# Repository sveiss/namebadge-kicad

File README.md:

namebadge-kicad
===============

This repo contains the Kicad data files for an animated desk toy/namebadge with the letter K, built using WS2812 LEDs (Adafruit "NeoPixels") and a Raspberry Pi Pico.

*Note*: This is my first electronics project in a very long while -- don't use this project as an example of how to do things right!

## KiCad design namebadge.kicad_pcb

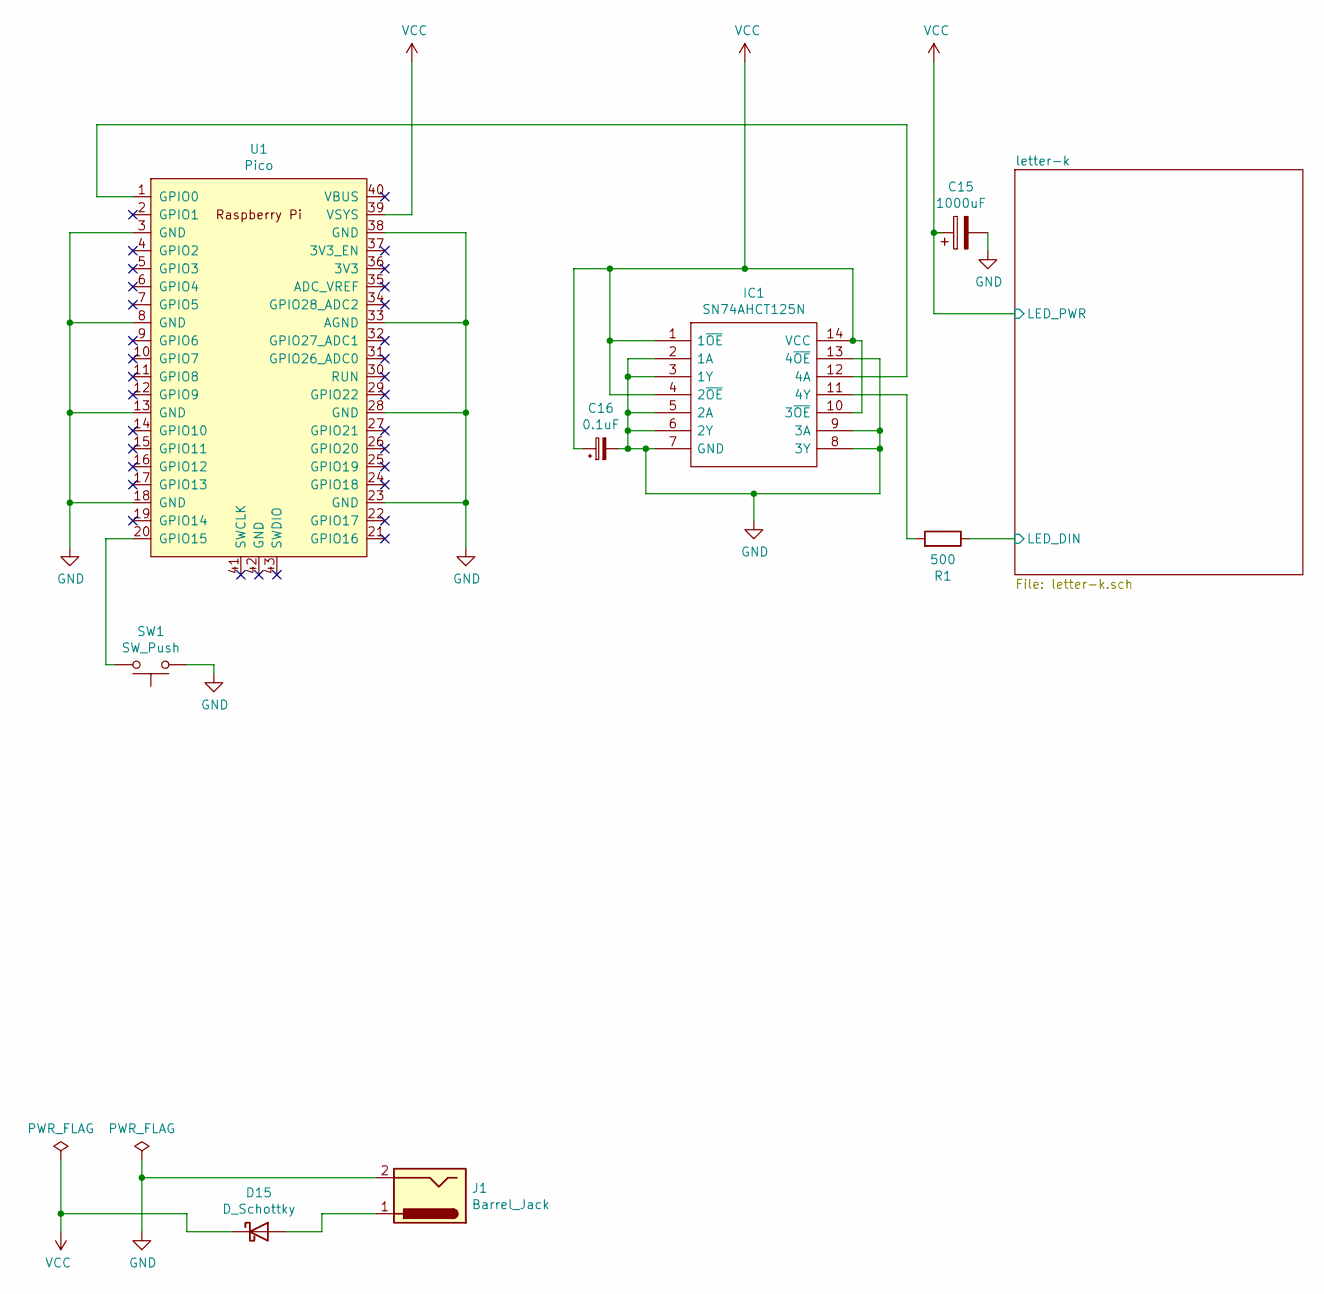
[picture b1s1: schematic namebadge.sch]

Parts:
C15: 1000uF; CP_Radial_D12.5mm_P5.00mm
C16: 0.1uF; C_Disc_D4.7mm_W2.5mm_P5.00mm
D15: D_Schottky; D_DO-41_SOD81_P10.16mm_Horizontal
IC1: SN74AHCT125N; DIP-14_W7.62mm; Manufacturer_Part_Number SN74AHCT125N; Mouser Part Number 595-SN74AHCT125N
J1: Barrel_Jack; BarrelJack_CUI_PJ-063AH_Horizontal
R1: 500; R_Axial_DIN0207_L6.3mm_D2.5mm_P10.16mm_Horizontal
SW1: SW_Push; SW_PUSH-12mm
U1: Pico; RPi_Pico_SMD_TH

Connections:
/letter-k/LED_DIN: R1.1; also elsewhere on the board
GND: C15.2, C16.2, IC1.2 (1A), IC1.3 (1Y), IC1.5 (2A), IC1.6 (2Y), IC1.7 (GND), IC1.8 (3Y), IC1.9 (3A), IC1.13 (4~OE), J1.2, SW1.1, U1.3 (GND), U1.8 (GND), U1.13 (GND), U1.18 (GND), U1.23 (GND), U1.28 (GND), U1.33 (AGND), U1.38 (GND); also elsewhere on the board
unnamed: D15.2 (A), J1.1
unnamed: IC1.11 (4Y), R1.2
unnamed: IC1.12 (4A), U1.1 (GPIO0)
unnamed: SW1.2, U1.20 (GPIO15)
VCC: C15.1, C16.1, D15.1 (K), IC1.1 (1~OE), IC1.4 (2~OE), IC1.10 (3~OE), IC1.14 (VCC), U1.39 (VSYS); also elsewhere on the board

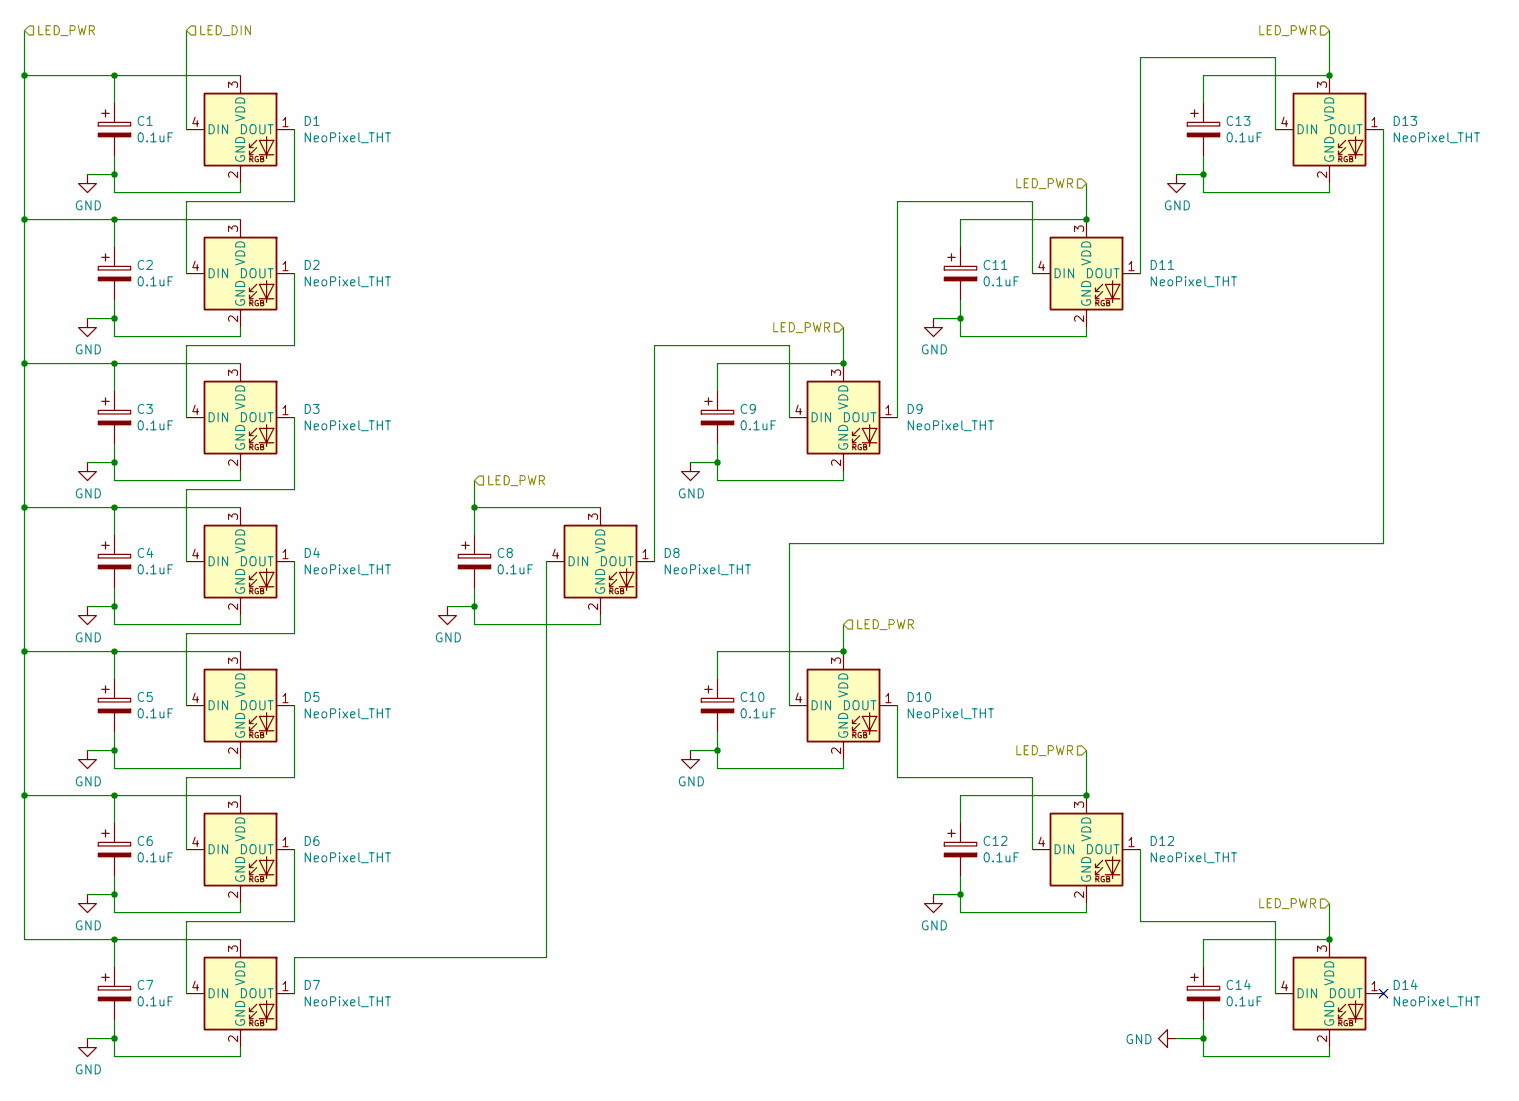
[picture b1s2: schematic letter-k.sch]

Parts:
C1, C2, C3, C4, C5, C6, C7, C8, C9, C10, C11, C12, C13, C14: 0.1uF; C_Disc_D4.7mm_W2.5mm_P5.00mm
D1, D2, D3, D4, D5, D6, D7, D8, D9, D10, D11, D12, D13, D14: NeoPixel_THT; LED_D5.0mm-4_RGB_Wide_Pins

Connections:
/letter-k/LED_DIN: D1.4 (DIN); also elsewhere on the board
GND: C1.2, C2.2, C3.2, C4.2, C5.2, C6.2, C7.2, C8.2, C9.2, C10.2, C11.2, C12.2, C13.2, C14.2, D1.2 (GND), D2.2 (GND), D3.2 (GND), D4.2 (GND), D5.2 (GND), D6.2 (GND), D7.2 (GND), D8.2 (GND), D9.2 (GND), D10.2 (GND), D11.2 (GND), D12.2 (GND), D13.2 (GND), D14.2 (GND); also elsewhere on the board
unnamed: D1.1 (DOUT), D2.4 (DIN)
unnamed: D2.1 (DOUT), D3.4 (DIN)
unnamed: D3.1 (DOUT), D4.4 (DIN)
unnamed: D4.1 (DOUT), D5.4 (DIN)
unnamed: D5.1 (DOUT), D6.4 (DIN)
unnamed: D6.1 (DOUT), D7.4 (DIN)
unnamed: D7.1 (DOUT), D8.4 (DIN)
unnamed: D8.1 (DOUT), D9.4 (DIN)
unnamed: D10.1 (DOUT), D12.4 (DIN)
unnamed: D10.4 (DIN), D13.1 (DOUT)
unnamed: D11.1 (DOUT), D13.4 (DIN)
unnamed: D9.1 (DOUT), D11.4 (DIN)
unnamed: D12.1 (DOUT), D14.4 (DIN)
VCC: C1.1, C2.1, C3.1, C4.1, C5.1, C6.1, C7.1, C8.1, C9.1, C10.1, C11.1, C12.1, C13.1, C14.1, D1.3 (VDD), D2.3 (VDD), D3.3 (VDD), D4.3 (VDD), D5.3 (VDD), D6.3 (VDD), D7.3 (VDD), D8.3 (VDD), D9.3 (VDD), D10.3 (VDD), D11.3 (VDD), D12.3 (VDD), D13.3 (VDD), D14.3 (VDD); also elsewhere on the board

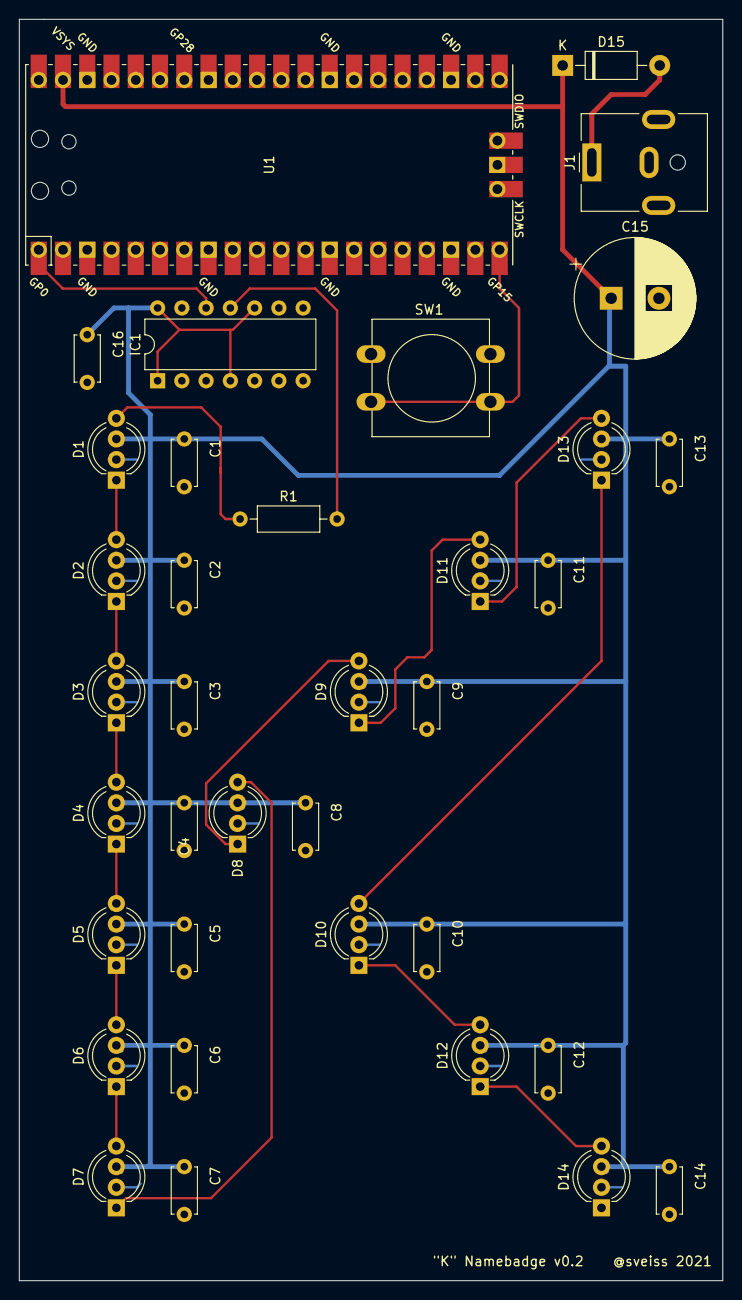
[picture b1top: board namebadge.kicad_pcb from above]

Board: 2 copper layers, 73.7 x 132.1 mm, 36 parts (0 on the bottom side), 20 nets.

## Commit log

2021-02-28 power cap
2021-02-28 level shifter
2021-02-28 DC jack take 1
2021-02-28 flip the pico
2021-02-28 fix traces after flip
2021-02-28 decoup for level shifter, layout cleanup
2021-02-28 switch
2021-02-28 fix dropped connection to gpio
2021-02-28 print setup
2021-02-28 3d model bits
2021-02-28 new renders
2021-03-12 add readme
2021-03-12 remove rendered gerbers
2021-03-12 Ground /OE on level shifter.
    Fixes #1.
2021-03-12 normalize endings
2021-03-18 Fix capacitor footprints and Pico location.
    Fixes #2, #3.
2021-03-18 Connect rest of pins on the buffer to VCC/Gnd. Resize copper plane to cover more of the Pico after its move. Fix a couple of unconnected tracks. PCB version on silkscreen to v0.2.
    Also updates schematic with capacitor footprint changes.
2021-03-18 Adds a Schottky on the DC input and moves it to VSYS, not VBUS.
    Fixes #4.
2021-03-18 Fix silkscreen for Pico
